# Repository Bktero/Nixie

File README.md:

# Nixie

Some circuit deal to deal with Nixie tubes.

## Power supply
The circuit was made to turn on ИН-14 (IH-14 with latin alphabet) tubes. The output voltage can be adjusted between 70 V and 240 V, making it suitable for other kinds of tubes.

You can find more information on this circuit on my blog (in French): https://gradot.wordpress.com/2015/03/10/alimentation-tubes-nixie/

## Time reference generator
The circuit generates a stable time reference. This is a square clock signal. Jumpers allow to select either 1 Hz, 2 Hz or 4 Hz as the output frequency.

You can find more information on this circuit on my blog (in French) : https://gradot.wordpress.com/2015/12/22/generer-un-signal-a-1-hz-avec-des-portes-logiques/

## Other circuits
Still work-in-progress attempts. Come back later :)

## License
_A copy of the license is available in this repository._

Copyright Pierre Gradot 2015-2016

This documentation describes Open Hardware and is licensed under the CERN OHL v. 1.2.

You may redistribute and modify this documentation under the terms of the CERN OHL v.1.2. (http://ohwr.org/cernohl).
This documentation is distributed WITHOUT ANY EXPRESS OR IMPLIED WARRANTY, INCLUDING OF MERCHANTABILITY, SATISFACTORY QUALITY AND FITNESS FOR APARTICULAR PURPOSE.

Please see the CERN OHL v.1.2 for applicable conditions.

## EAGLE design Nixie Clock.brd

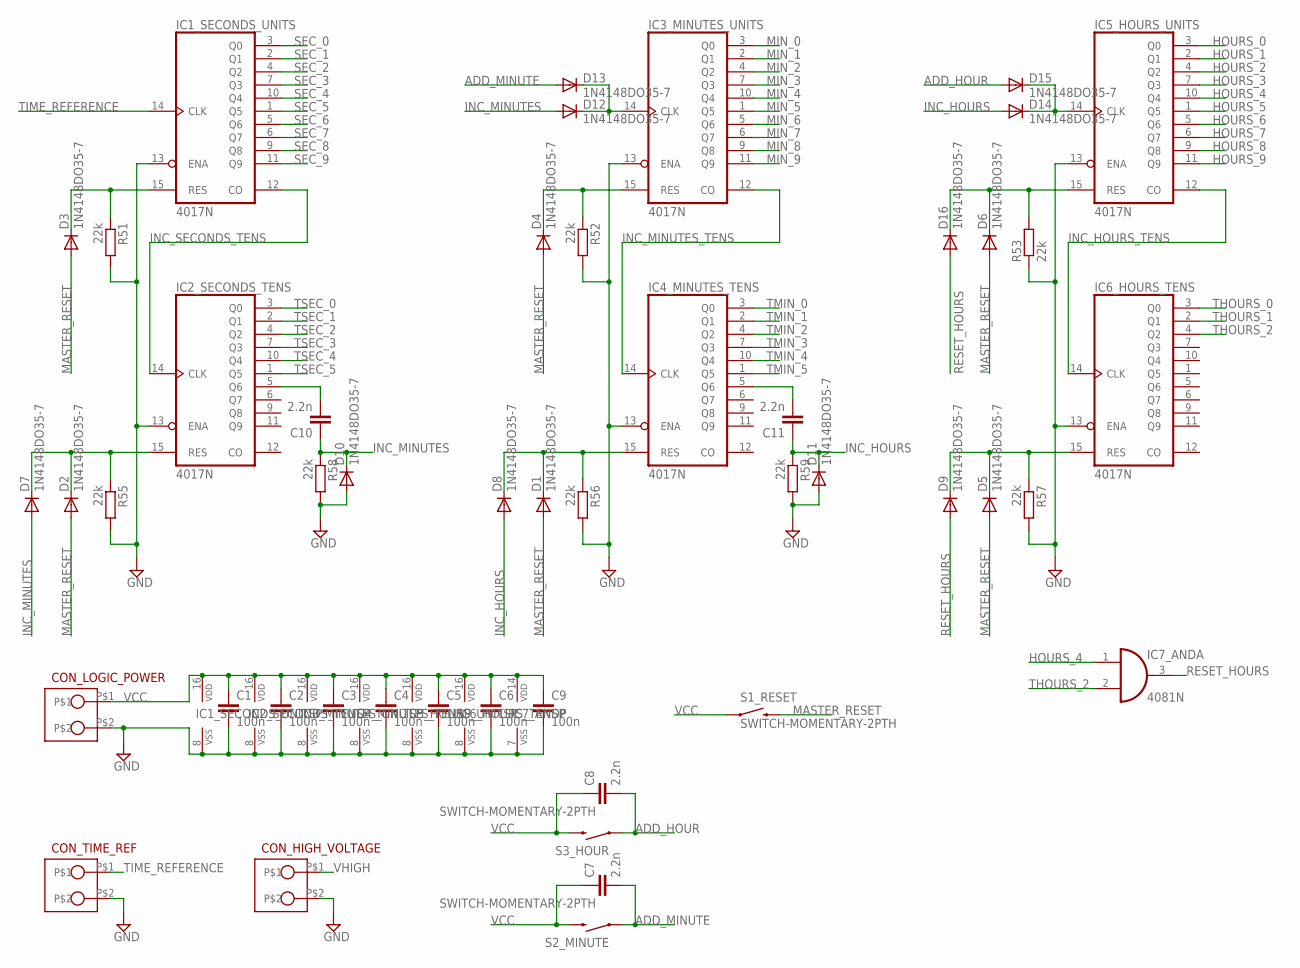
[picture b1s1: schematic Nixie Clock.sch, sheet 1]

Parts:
C1, C2, C3, C4, C5, C6, C9: 100n; C050-030X075
C7, C8, C10, C11: 2.2n; C050-030X075
CON_HIGH_VOLTAGE: CON_2_SIL; SIL_2_0.2INCH
CON_LOGIC_POWER: CON_2_SIL; SIL_2_0.2INCH
CON_TIME_REF: CON_2_SIL; SIL_2_0.2INCH
D1, D2, D3, D4, D5, D6, D7, D8, D9, D10, D11, D12, D13, D14, D15, D16: 1N4148DO35-7; DO35-7
IC1_SECONDS_UNITS, IC2_SECONDS_TENS, IC3_MINUTES_UNITS, IC4_MINUTES_TENS, IC5_HOURS_UNITS, IC6_HOURS_TENS: 4017N; DIL16
IC7_AND: 4081N; DIL14
R51, R52, R53, R55, R56, R57, R58, R59: 22k; 0207/10
S1_RESET, S2_MINUTE, S3_HOUR: SWITCH-MOMENTARY-2PTH; TACTILE-PTH

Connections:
ADD_HOUR: C8.2, D15.A, S3_HOUR.1
ADD_MINUTE: C7.2, D13.A, S2_MINUTE.1
GND: C1.2, C2.2, C3.2, C4.2, C5.2, C6.2, C9.2, CON_HIGH_VOLTAGE.P$2, CON_LOGIC_POWER.P$2, CON_TIME_REF.P$2, D10.A, D11.A, IC1_SECONDS_UNITS.8 (VSS), IC1_SECONDS_UNITS.13 (ENA), IC2_SECONDS_TENS.8 (VSS), IC2_SECONDS_TENS.13 (ENA), IC3_MINUTES_UNITS.8 (VSS), IC3_MINUTES_UNITS.13 (ENA), IC4_MINUTES_TENS.8 (VSS), IC4_MINUTES_TENS.13 (ENA), IC5_HOURS_UNITS.8 (VSS), IC5_HOURS_UNITS.13 (ENA), IC6_HOURS_TENS.8 (VSS), IC6_HOURS_TENS.13 (ENA), IC7_AND.7 (VSS), R51.2, R52.2, R53.1, R55.2, R56.2, R57.2, R58.2, R59.2; also elsewhere on the board
HOURS_0: IC5_HOURS_UNITS.3 (Q0); also elsewhere on the board
HOURS_1: IC5_HOURS_UNITS.2 (Q1); also elsewhere on the board
HOURS_2: IC5_HOURS_UNITS.4 (Q2); also elsewhere on the board
HOURS_3: IC5_HOURS_UNITS.7 (Q3); also elsewhere on the board
HOURS_4: IC5_HOURS_UNITS.10 (Q4), IC7_AND.1 (I0); also elsewhere on the board
HOURS_5: IC5_HOURS_UNITS.1 (Q5); also elsewhere on the board
HOURS_6: IC5_HOURS_UNITS.5 (Q6); also elsewhere on the board
HOURS_7: IC5_HOURS_UNITS.6 (Q7); also elsewhere on the board
HOURS_8: IC5_HOURS_UNITS.9 (Q8); also elsewhere on the board
HOURS_9: IC5_HOURS_UNITS.11 (Q9); also elsewhere on the board
INC_HOURS: C11.1, D8.A, D11.C, D14.A, R59.1
INC_HOURS_TENS: IC5_HOURS_UNITS.12 (CO), IC6_HOURS_TENS.14 (CLK)
INC_MINUTES: C10.1, D7.A, D10.C, D12.A, R58.1
INC_MINUTES_TENS: IC3_MINUTES_UNITS.12 (CO), IC4_MINUTES_TENS.14 (CLK)
INC_SECONDS_TENS: IC1_SECONDS_UNITS.12 (CO), IC2_SECONDS_TENS.14 (CLK)
MASTER_RESET: D1.A, D2.A, D3.A, D4.A, D5.A, D6.A, S1_RESET.3 (2)
MIN_0: IC3_MINUTES_UNITS.3 (Q0); also elsewhere on the board
MIN_1: IC3_MINUTES_UNITS.2 (Q1); also elsewhere on the board
MIN_2: IC3_MINUTES_UNITS.4 (Q2); also elsewhere on the board
MIN_3: IC3_MINUTES_UNITS.7 (Q3); also elsewhere on the board
MIN_4: IC3_MINUTES_UNITS.10 (Q4); also elsewhere on the board
MIN_5: IC3_MINUTES_UNITS.1 (Q5); also elsewhere on the board
MIN_6: IC3_MINUTES_UNITS.5 (Q6); also elsewhere on the board
MIN_7: IC3_MINUTES_UNITS.6 (Q7); also elsewhere on the board
MIN_8: IC3_MINUTES_UNITS.9 (Q8); also elsewhere on the board
MIN_9: IC3_MINUTES_UNITS.11 (Q9); also elsewhere on the board
unnamed: D2.C, D7.C, IC2_SECONDS_TENS.15 (RES), R55.1
unnamed: D3.C, IC1_SECONDS_UNITS.15 (RES), R51.1
unnamed: C10.2, IC2_SECONDS_TENS.5 (Q6)
unnamed: D1.C, D8.C, IC4_MINUTES_TENS.15 (RES), R56.1
unnamed: C11.2, IC4_MINUTES_TENS.5 (Q6)
unnamed: D4.C, IC3_MINUTES_UNITS.15 (RES), R52.1
unnamed: D12.C, D13.C, IC3_MINUTES_UNITS.14 (CLK)
unnamed: D5.C, D9.C, IC6_HOURS_TENS.15 (RES), R57.1
unnamed: D14.C, D15.C, IC5_HOURS_UNITS.14 (CLK)
unnamed: D6.C, D16.C, IC5_HOURS_UNITS.15 (RES), R53.2
RESET_HOURS: D9.A, D16.A, IC7_AND.3 (O)
SEC_0: IC1_SECONDS_UNITS.3 (Q0); also elsewhere on the board
SEC_1: IC1_SECONDS_UNITS.2 (Q1); also elsewhere on the board
SEC_2: IC1_SECONDS_UNITS.4 (Q2); also elsewhere on the board
SEC_3: IC1_SECONDS_UNITS.7 (Q3); also elsewhere on the board
SEC_4: IC1_SECONDS_UNITS.10 (Q4); also elsewhere on the board
SEC_5: IC1_SECONDS_UNITS.1 (Q5); also elsewhere on the board
SEC_6: IC1_SECONDS_UNITS.5 (Q6); also elsewhere on the board
SEC_7: IC1_SECONDS_UNITS.6 (Q7); also elsewhere on the board
SEC_8: IC1_SECONDS_UNITS.9 (Q8); also elsewhere on the board
SEC_9: IC1_SECONDS_UNITS.11 (Q9); also elsewhere on the board
THOURS_0: IC6_HOURS_TENS.3 (Q0); also elsewhere on the board
THOURS_1: IC6_HOURS_TENS.2 (Q1); also elsewhere on the board
THOURS_2: IC6_HOURS_TENS.4 (Q2), IC7_AND.2 (I1); also elsewhere on the board
TIME_REFERENCE: CON_TIME_REF.P$1, IC1_SECONDS_UNITS.14 (CLK)
TMIN_0: IC4_MINUTES_TENS.3 (Q0); also elsewhere on the board
TMIN_1: IC4_MINUTES_TENS.2 (Q1); also elsewhere on the board
TMIN_2: IC4_MINUTES_TENS.4 (Q2); also elsewhere on the board
TMIN_3: IC4_MINUTES_TENS.7 (Q3); also elsewhere on the board
TMIN_4: IC4_MINUTES_TENS.10 (Q4); also elsewhere on the board
TMIN_5: IC4_MINUTES_TENS.1 (Q5); also elsewhere on the board
TSEC_0: IC2_SECONDS_TENS.3 (Q0); also elsewhere on the board
TSEC_1: IC2_SECONDS_TENS.2 (Q1); also elsewhere on the board
TSEC_2: IC2_SECONDS_TENS.4 (Q2); also elsewhere on the board
TSEC_3: IC2_SECONDS_TENS.7 (Q3); also elsewhere on the board
TSEC_4: IC2_SECONDS_TENS.10 (Q4); also elsewhere on the board
TSEC_5: IC2_SECONDS_TENS.1 (Q5); also elsewhere on the board
VCC: C1.1, C2.1, C3.1, C4.1, C5.1, C6.1, C7.1, C8.1, C9.1, CON_LOGIC_POWER.P$1, IC1_SECONDS_UNITS.16 (VDD), IC2_SECONDS_TENS.16 (VDD), IC3_MINUTES_UNITS.16 (VDD), IC4_MINUTES_TENS.16 (VDD), IC5_HOURS_UNITS.16 (VDD), IC6_HOURS_TENS.16 (VDD), IC7_AND.14 (VDD), S1_RESET.1, S2_MINUTE.3 (2), S3_HOUR.3 (2)
VHIGH: CON_HIGH_VOLTAGE.P$1; also elsewhere on the board

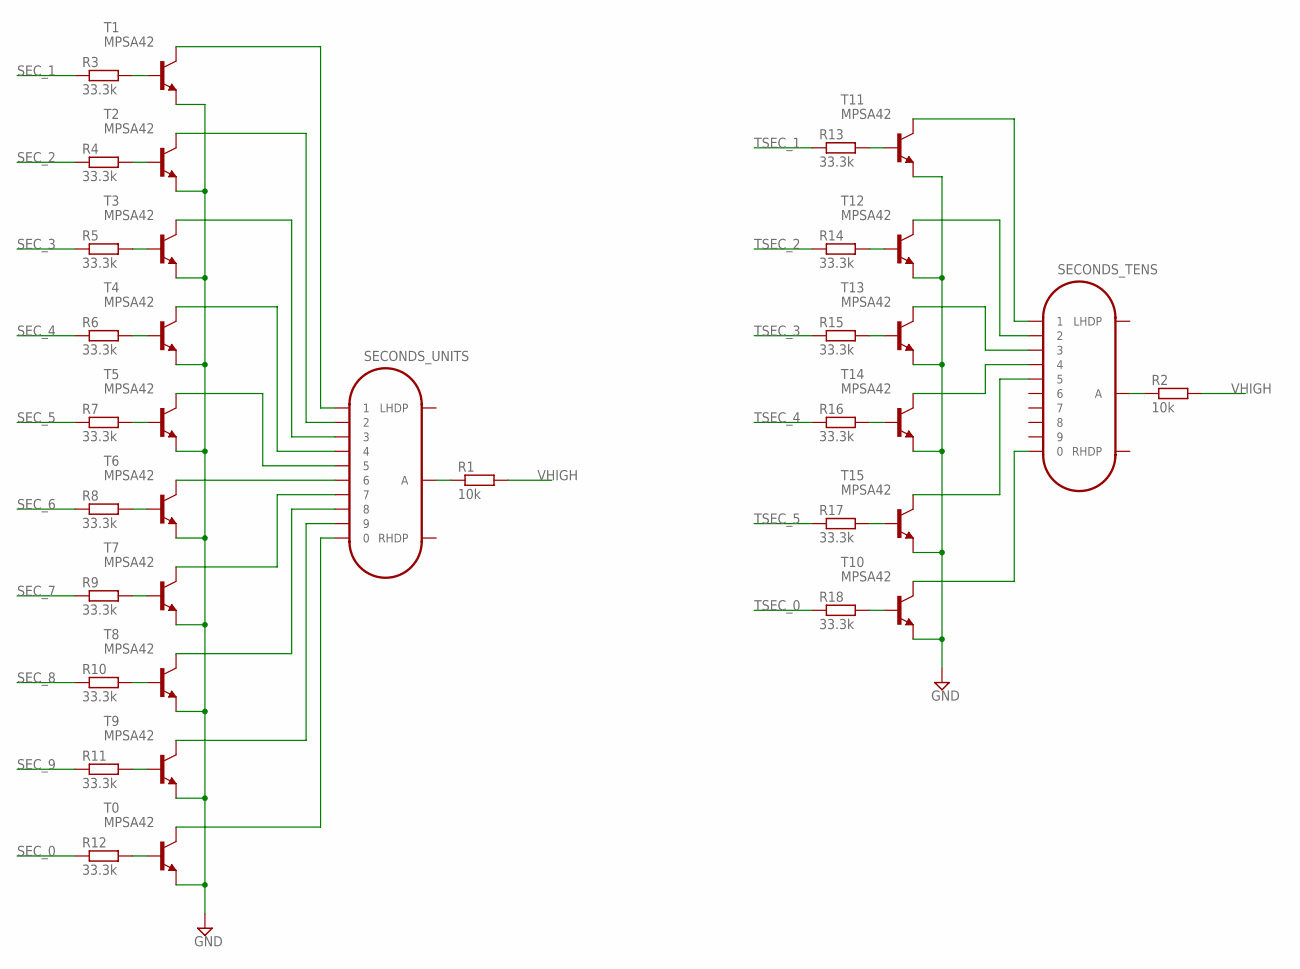
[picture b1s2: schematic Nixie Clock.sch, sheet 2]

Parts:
R1, R2: 10k; 0207/2V
R3, R4, R5, R6, R7, R8, R9, R10, R11, R12, R13, R14, R15, R16, R17, R18: 33.3k; 0207/10
SECONDS_TENS: IN-14BIG_PADS; IN-14-BIG-PADS
SECONDS_UNITS: IN-14BIG_PADS; IN-14-BIG-PADS
T0, T1, T2, T3, T4, T5, T6, T7, T8, T9, T10, T11, T12, T13, T14, T15: MPSA42; TO92

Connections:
GND: T0.1 (E), T1.1 (E), T2.1 (E), T3.1 (E), T4.1 (E), T5.1 (E), T6.1 (E), T7.1 (E), T8.1 (E), T9.1 (E), T10.1 (E), T11.1 (E), T12.1 (E), T13.1 (E), T14.1 (E), T15.1 (E); also elsewhere on the board
unnamed: R6.2, T4.2 (B)
unnamed: R7.2, T5.2 (B)
unnamed: R8.2, T6.2 (B)
unnamed: R9.2, T7.2 (B)
unnamed: R10.2, T8.2 (B)
unnamed: R11.2, T9.2 (B)
unnamed: R12.2, T0.2 (B)
unnamed: R1.1, SECONDS_UNITS.A
unnamed: R2.1, SECONDS_TENS.A
unnamed: R13.2, T11.2 (B)
unnamed: R14.2, T12.2 (B)
unnamed: R15.2, T13.2 (B)
unnamed: R16.2, T14.2 (B)
unnamed: R17.2, T15.2 (B)
unnamed: R18.2, T10.2 (B)
unnamed: R3.2, T1.2 (B)
unnamed: R4.2, T2.2 (B)
unnamed: R5.2, T3.2 (B)
unnamed: SECONDS_TENS.1, T11.3 (C)
unnamed: SECONDS_TENS.2, T12.3 (C)
unnamed: SECONDS_TENS.3, T13.3 (C)
unnamed: SECONDS_TENS.4, T14.3 (C)
unnamed: SECONDS_TENS.5, T15.3 (C)
unnamed: SECONDS_TENS.0, T10.3 (C)
unnamed: SECONDS_UNITS.1, T1.3 (C)
unnamed: SECONDS_UNITS.2, T2.3 (C)
unnamed: SECONDS_UNITS.3, T3.3 (C)
unnamed: SECONDS_UNITS.4, T4.3 (C)
unnamed: SECONDS_UNITS.5, T5.3 (C)
unnamed: SECONDS_UNITS.6, T6.3 (C)
unnamed: SECONDS_UNITS.0, T0.3 (C)
unnamed: SECONDS_UNITS.9, T9.3 (C)
unnamed: SECONDS_UNITS.8, T8.3 (C)
unnamed: SECONDS_UNITS.7, T7.3 (C)
SEC_0: R12.1; also elsewhere on the board
SEC_1: R3.1; also elsewhere on the board
SEC_2: R4.1; also elsewhere on the board
SEC_3: R5.1; also elsewhere on the board
SEC_4: R6.1; also elsewhere on the board
SEC_5: R7.1; also elsewhere on the board
SEC_6: R8.1; also elsewhere on the board
SEC_7: R9.1; also elsewhere on the board
SEC_8: R10.1; also elsewhere on the board
SEC_9: R11.1; also elsewhere on the board
TSEC_0: R18.1; also elsewhere on the board
TSEC_1: R13.1; also elsewhere on the board
TSEC_2: R14.1; also elsewhere on the board
TSEC_3: R15.1; also elsewhere on the board
TSEC_4: R16.1; also elsewhere on the board
TSEC_5: R17.1; also elsewhere on the board
VHIGH: R1.2, R2.2; also elsewhere on the board

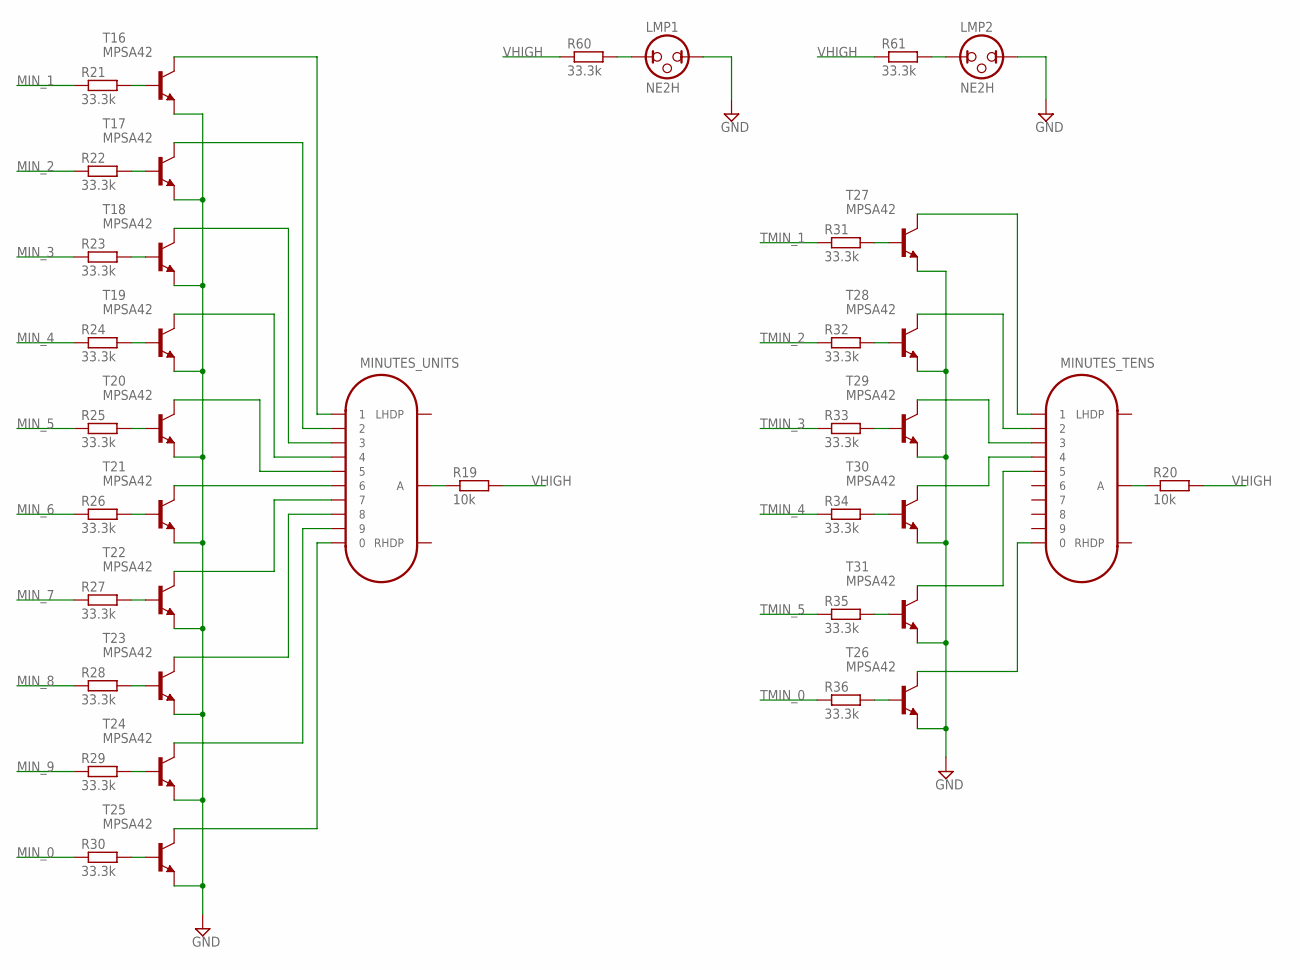
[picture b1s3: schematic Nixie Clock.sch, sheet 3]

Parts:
LMP1, LMP2: NE2H; NEON_LAMP_0.1_INCH
MINUTES_TENS: IN-14BIG_PADS; IN-14-BIG-PADS
MINUTES_UNITS: IN-14BIG_PADS; IN-14-BIG-PADS
R19, R20: 10k; 0207/2V
R21, R22, R23, R24, R25, R26, R27, R28, R29, R30, R31, R32, R33, R34, R35, R36: 33.3k; 0207/10
R60, R61: 33.3k; 0207/2V
T16, T17, T18, T19, T20, T21, T22, T23, T24, T25, T26, T27, T28, T29, T30, T31: MPSA42; TO92

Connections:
GND: LMP1.P$2 (2), LMP2.P$2 (2), T16.1 (E), T17.1 (E), T18.1 (E), T19.1 (E), T20.1 (E), T21.1 (E), T22.1 (E), T23.1 (E), T24.1 (E), T25.1 (E), T26.1 (E), T27.1 (E), T28.1 (E), T29.1 (E), T30.1 (E), T31.1 (E); also elsewhere on the board
MIN_0: R30.1; also elsewhere on the board
MIN_1: R21.1; also elsewhere on the board
MIN_2: R22.1; also elsewhere on the board
MIN_3: R23.1; also elsewhere on the board
MIN_4: R24.1; also elsewhere on the board
MIN_5: R25.1; also elsewhere on the board
MIN_6: R26.1; also elsewhere on the board
MIN_7: R27.1; also elsewhere on the board
MIN_8: R28.1; also elsewhere on the board
MIN_9: R29.1; also elsewhere on the board
unnamed: R24.2, T19.2 (B)
unnamed: R25.2, T20.2 (B)
unnamed: R26.2, T21.2 (B)
unnamed: R27.2, T22.2 (B)
unnamed: R28.2, T23.2 (B)
unnamed: R29.2, T24.2 (B)
unnamed: R30.2, T25.2 (B)
unnamed: MINUTES_UNITS.A, R19.1
unnamed: MINUTES_TENS.A, R20.1
unnamed: R31.2, T27.2 (B)
unnamed: R32.2, T28.2 (B)
unnamed: R33.2, T29.2 (B)
unnamed: R34.2, T30.2 (B)
unnamed: R35.2, T31.2 (B)
unnamed: R36.2, T26.2 (B)
unnamed: R21.2, T16.2 (B)
unnamed: R22.2, T17.2 (B)
unnamed: R23.2, T18.2 (B)
unnamed: MINUTES_TENS.1, T27.3 (C)
unnamed: MINUTES_TENS.2, T28.3 (C)
unnamed: MINUTES_TENS.3, T29.3 (C)
unnamed: MINUTES_TENS.4, T30.3 (C)
unnamed: MINUTES_TENS.5, T31.3 (C)
unnamed: MINUTES_TENS.0, T26.3 (C)
unnamed: MINUTES_UNITS.1, T16.3 (C)
unnamed: MINUTES_UNITS.2, T17.3 (C)
unnamed: MINUTES_UNITS.3, T18.3 (C)
unnamed: MINUTES_UNITS.4, T19.3 (C)
unnamed: MINUTES_UNITS.5, T20.3 (C)
unnamed: MINUTES_UNITS.6, T21.3 (C)
unnamed: MINUTES_UNITS.0, T25.3 (C)
unnamed: MINUTES_UNITS.9, T24.3 (C)
unnamed: MINUTES_UNITS.8, T23.3 (C)
unnamed: MINUTES_UNITS.7, T22.3 (C)
unnamed: LMP2.P$1 (1), R61.2
unnamed: LMP1.P$1 (1), R60.2
TMIN_0: R36.1; also elsewhere on the board
TMIN_1: R31.1; also elsewhere on the board
TMIN_2: R32.1; also elsewhere on the board
TMIN_3: R33.1; also elsewhere on the board
TMIN_4: R34.1; also elsewhere on the board
TMIN_5: R35.1; also elsewhere on the board
VHIGH: R19.2, R20.2, R60.1, R61.1; also elsewhere on the board

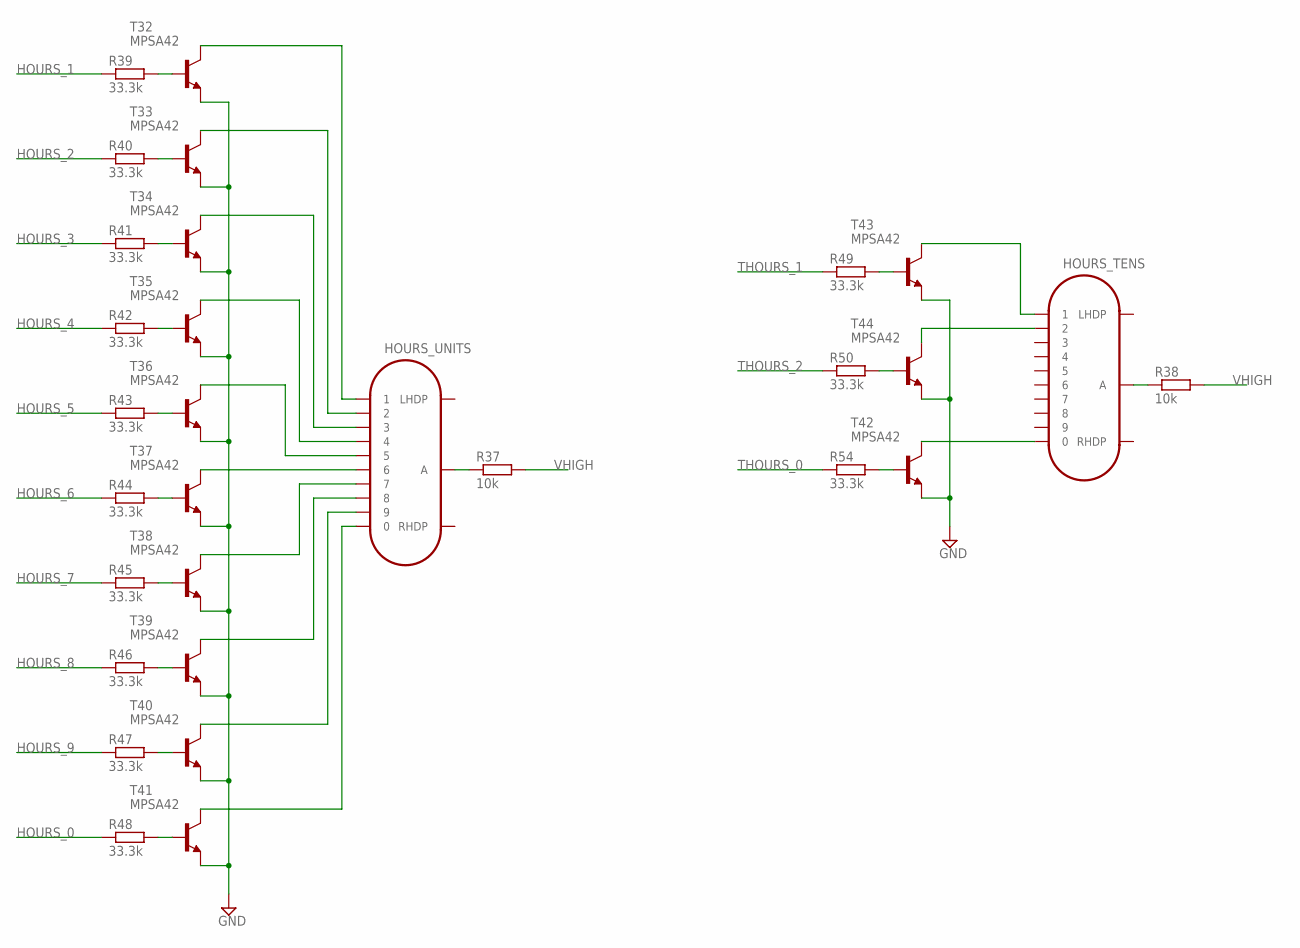
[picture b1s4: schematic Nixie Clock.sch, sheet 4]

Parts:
HOURS_TENS: IN-14BIG_PADS; IN-14-BIG-PADS
HOURS_UNITS: IN-14BIG_PADS; IN-14-BIG-PADS
R37, R38: 10k; 0207/2V
R39, R40, R41, R42, R43, R44, R45, R46, R47, R48, R49, R50, R54: 33.3k; 0207/10
T32, T33, T34, T35, T36, T37, T38, T39, T40, T41, T42, T43, T44: MPSA42; TO92

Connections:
GND: T32.1 (E), T33.1 (E), T34.1 (E), T35.1 (E), T36.1 (E), T37.1 (E), T38.1 (E), T39.1 (E), T40.1 (E), T41.1 (E), T42.1 (E), T43.1 (E), T44.1 (E); also elsewhere on the board
HOURS_0: R48.1; also elsewhere on the board
HOURS_1: R39.1; also elsewhere on the board
HOURS_2: R40.1; also elsewhere on the board
HOURS_3: R41.1; also elsewhere on the board
HOURS_4: R42.1; also elsewhere on the board
HOURS_5: R43.1; also elsewhere on the board
HOURS_6: R44.1; also elsewhere on the board
HOURS_7: R45.1; also elsewhere on the board
HOURS_8: R46.1; also elsewhere on the board
HOURS_9: R47.1; also elsewhere on the board
unnamed: R42.2, T35.2 (B)
unnamed: R43.2, T36.2 (B)
unnamed: R44.2, T37.2 (B)
unnamed: R45.2, T38.2 (B)
unnamed: R46.2, T39.2 (B)
unnamed: R47.2, T40.2 (B)
unnamed: R48.2, T41.2 (B)
unnamed: HOURS_UNITS.A, R37.1
unnamed: HOURS_TENS.A, R38.1
unnamed: R49.2, T43.2 (B)
unnamed: R50.2, T44.2 (B)
unnamed: HOURS_TENS.0, T42.3 (C)
unnamed: R54.2, T42.2 (B)
unnamed: R39.2, T32.2 (B)
unnamed: R40.2, T33.2 (B)
unnamed: R41.2, T34.2 (B)
unnamed: HOURS_TENS.1, T43.3 (C)
unnamed: HOURS_TENS.2, T44.3 (C)
unnamed: HOURS_UNITS.7, T38.3 (C)
unnamed: HOURS_UNITS.1, T32.3 (C)
unnamed: HOURS_UNITS.2, T33.3 (C)
unnamed: HOURS_UNITS.3, T34.3 (C)
unnamed: HOURS_UNITS.4, T35.3 (C)
unnamed: HOURS_UNITS.5, T36.3 (C)
unnamed: HOURS_UNITS.6, T37.3 (C)
unnamed: HOURS_UNITS.0, T41.3 (C)
unnamed: HOURS_UNITS.9, T40.3 (C)
unnamed: HOURS_UNITS.8, T39.3 (C)
THOURS_0: R54.1; also elsewhere on the board
THOURS_1: R49.1; also elsewhere on the board
THOURS_2: R50.1; also elsewhere on the board
VHIGH: R37.2, R38.2; also elsewhere on the board

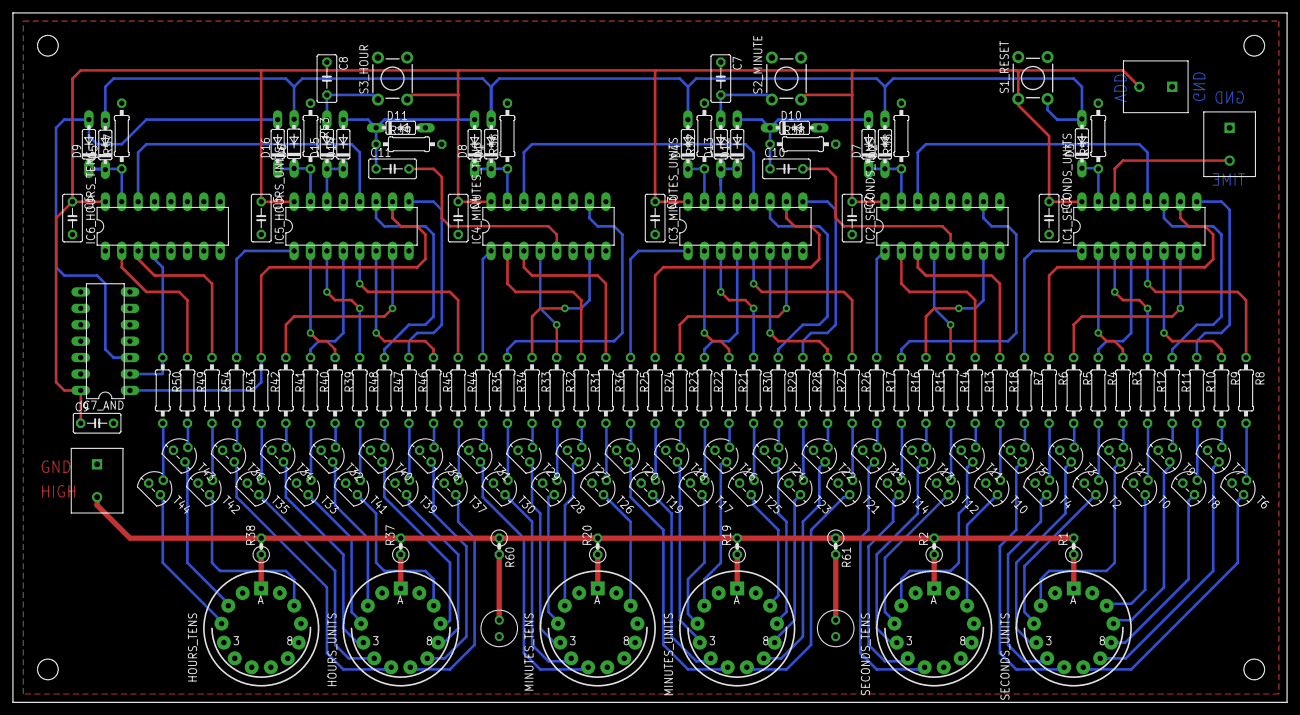
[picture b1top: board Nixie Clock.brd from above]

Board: 2 copper layers, 197.2 x 106.7 mm, 154 parts (0 on the bottom side), 166 nets.

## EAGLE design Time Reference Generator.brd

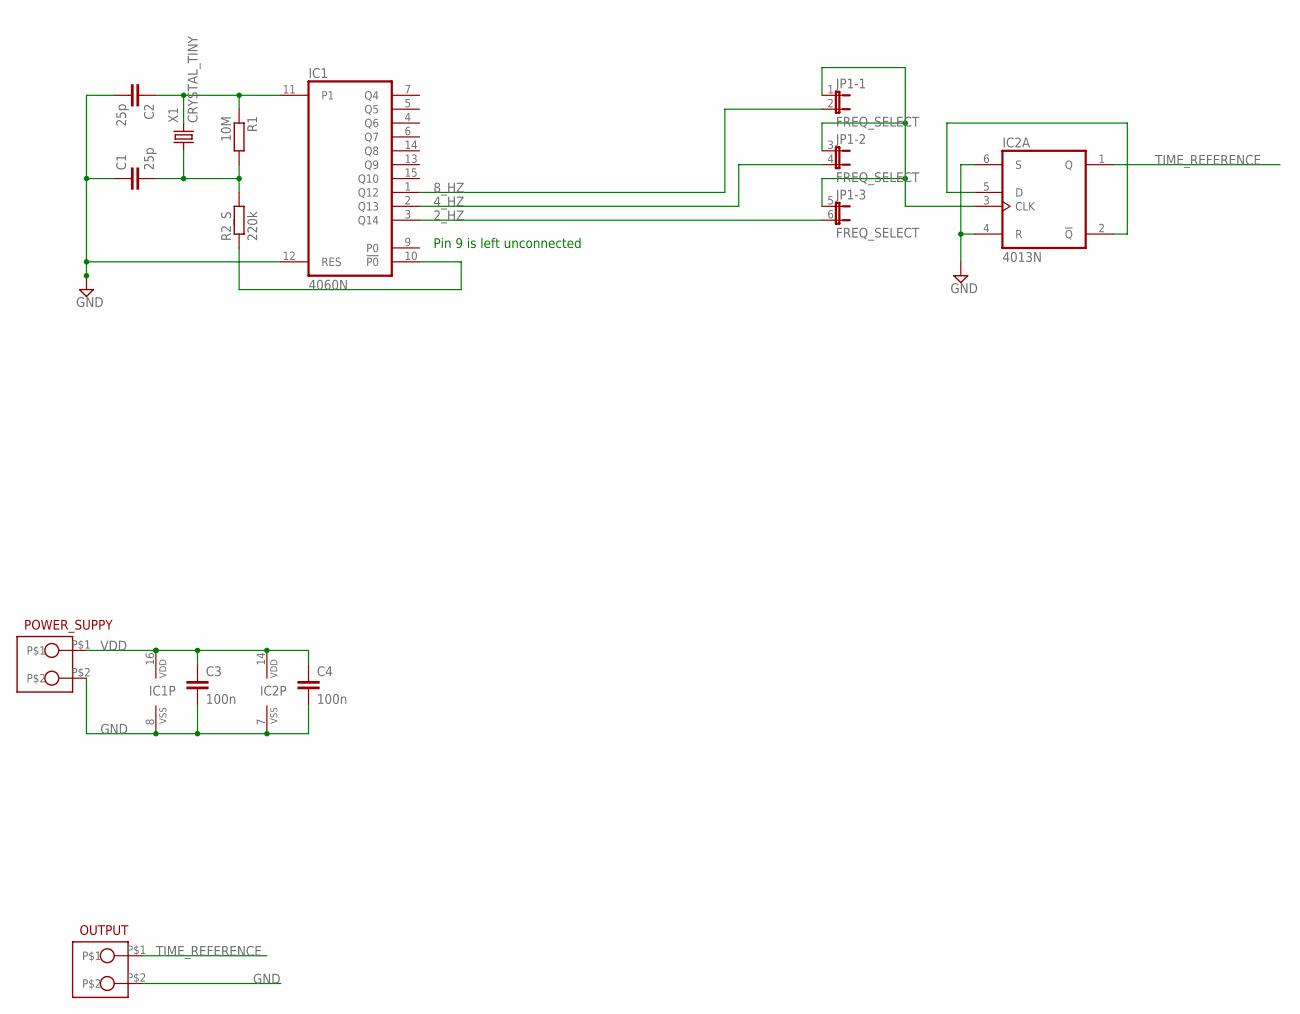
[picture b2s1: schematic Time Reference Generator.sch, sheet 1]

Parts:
C1, C2: 25p; C050-025X075
C3, C4: 100n; C050-030X075
IC1: 4060N; DIL16
IC2: 4013N; DIL14
JP1: FREQ_SELECT; JP3Q
OUTPUT: CON_2_SIL; SIL_2_0.2INCH
POWER_SUPPY: CON_2_SIL; SIL_2_0.2INCH
R1: 10M; 0207/10
R2_S: 220k; 0207/10
X1: CRYSTAL_TINY; WATCH-3X8-SPACED

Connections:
2_HZ: IC1.3 (Q14), JP1.6 (2)
4_HZ: IC1.2 (Q13), JP1.4 (2)
8_HZ: IC1.1 (Q12), JP1.2
GND: C1.1, C2.2, C3.2, C4.2, IC1.8 (VSS), IC1.12 (RES), IC2.4 (R), IC2.6 (S), IC2.7 (VSS), OUTPUT.P$2, POWER_SUPPY.P$2
unnamed: C2.1, IC1.11 (P1), R1.1, X1.2
unnamed: C1.2, R1.2, R2_S.2, X1.1
unnamed: IC1.10 (!P0), R2_S.1
unnamed: IC2.2 (!Q), IC2.5 (D)
unnamed: IC2.3 (CLK), JP1.1, JP1.3 (1), JP1.5 (1)
TIME_REFERENCE: IC2.1 (Q), OUTPUT.P$1
VDD: C3.1, C4.1, IC1.16 (VDD), IC2.14 (VDD), POWER_SUPPY.P$1

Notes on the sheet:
Pin 9 is left unconnected

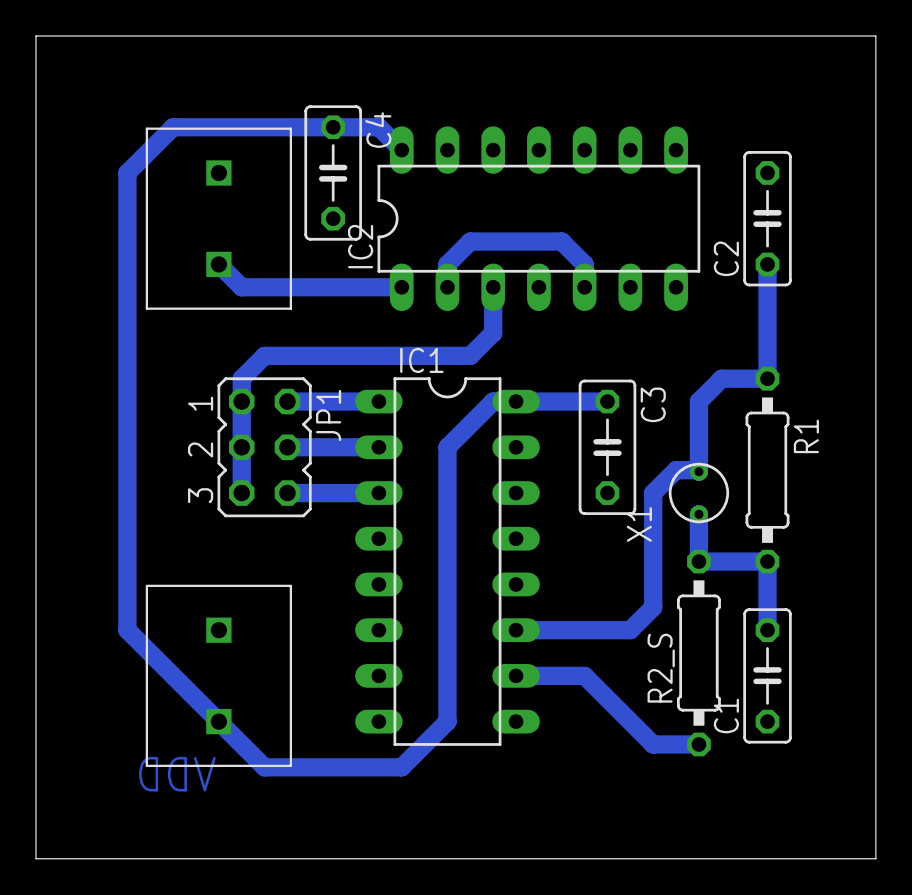
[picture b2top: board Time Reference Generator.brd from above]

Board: 2 copper layers, 46.7 x 45.7 mm, 12 parts (0 on the bottom side), 11 nets.

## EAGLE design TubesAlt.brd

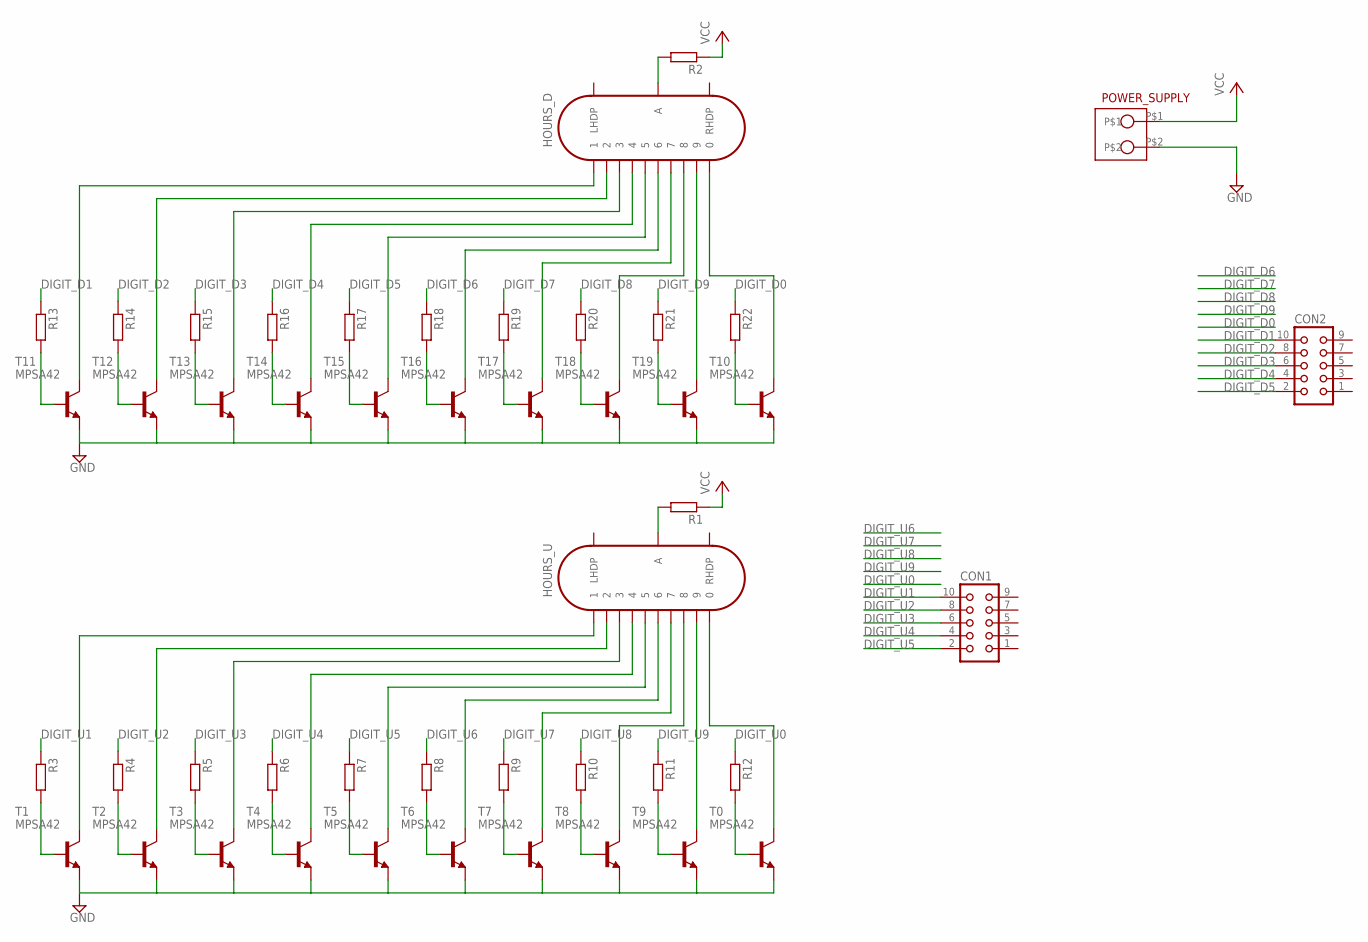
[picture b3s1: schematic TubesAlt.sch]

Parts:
CON1, CON2: CON10
HOURS_D: IN-14
HOURS_U: IN-14
POWER_SUPPLY: CON_2_SIL; SIL_2_0.2INCH
R1, R2, R3, R4, R5, R6, R7, R8, R9, R10, R11, R12, R13, R14, R15, R16, R17, R18, R19, R20, R21, R22: R-EU_0207/10; 0207/10
T0, T1, T2, T3, T4, T5, T6, T7, T8, T9, T10, T11, T12, T13, T14, T15, T16, T17, T18, T19: MPSA42; TO92

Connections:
DIGIT_D0: R22.1
DIGIT_D1: CON2.10, R13.1
DIGIT_D2: CON2.8, R14.1
DIGIT_D3: CON2.6, R15.1
DIGIT_D4: CON2.4, R16.1
DIGIT_D5: CON2.2, R17.1
DIGIT_D6: R18.1
DIGIT_D7: R19.1
DIGIT_D8: R20.1
DIGIT_D9: R21.1
DIGIT_U0: R12.1
DIGIT_U1: CON1.10, R3.1
DIGIT_U2: CON1.8, R4.1
DIGIT_U3: CON1.6, R5.1
DIGIT_U4: CON1.4, R6.1
DIGIT_U5: CON1.2, R7.1
DIGIT_U6: R8.1
DIGIT_U7: R9.1
DIGIT_U8: R10.1
DIGIT_U9: R11.1
GND: POWER_SUPPLY.P$2, T0.1 (E), T1.1 (E), T2.1 (E), T3.1 (E), T4.1 (E), T5.1 (E), T6.1 (E), T7.1 (E), T8.1 (E), T9.1 (E), T10.1 (E), T11.1 (E), T12.1 (E), T13.1 (E), T14.1 (E), T15.1 (E), T16.1 (E), T17.1 (E), T18.1 (E), T19.1 (E)
unnamed: HOURS_U.0, T0.3 (C)
unnamed: HOURS_U.9, T9.3 (C)
unnamed: R7.2, T5.2 (B)
unnamed: R8.2, T6.2 (B)
unnamed: R9.2, T7.2 (B)
unnamed: R12.2, T0.2 (B)
unnamed: R3.2, T1.2 (B)
unnamed: R5.2, T3.2 (B)
unnamed: R4.2, T2.2 (B)
unnamed: R6.2, T4.2 (B)
unnamed: R10.2, T8.2 (B)
unnamed: R11.2, T9.2 (B)
unnamed: HOURS_U.8, T8.3 (C)
unnamed: HOURS_U.7, T7.3 (C)
unnamed: HOURS_U.6, T6.3 (C)
unnamed: HOURS_U.5, T5.3 (C)
unnamed: HOURS_U.1, T1.3 (C)
unnamed: HOURS_U.4, T4.3 (C)
unnamed: HOURS_U.2, T2.3 (C)
unnamed: HOURS_D.0, T10.3 (C)
unnamed: HOURS_U.3, T3.3 (C)
unnamed: HOURS_D.9, T19.3 (C)
unnamed: HOURS_U.A, R1.2
unnamed: HOURS_D.8, T18.3 (C)
unnamed: HOURS_D.7, T17.3 (C)
unnamed: HOURS_D.6, T16.3 (C)
unnamed: HOURS_D.5, T15.3 (C)
unnamed: HOURS_D.2, T12.3 (C)
unnamed: HOURS_D.A, R2.2
unnamed: HOURS_D.3, T13.3 (C)
unnamed: HOURS_D.4, T14.3 (C)
unnamed: HOURS_D.1, T11.3 (C)
unnamed: R17.2, T15.2 (B)
unnamed: R18.2, T16.2 (B)
unnamed: R19.2, T17.2 (B)
unnamed: R22.2, T10.2 (B)
unnamed: R13.2, T11.2 (B)
unnamed: R15.2, T13.2 (B)
unnamed: R14.2, T12.2 (B)
unnamed: R16.2, T14.2 (B)
unnamed: R20.2, T18.2 (B)
unnamed: R21.2, T19.2 (B)
VCC: POWER_SUPPLY.P$1, R1.1, R2.1

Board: 2 copper layers, 47 parts (0 on the bottom side), 54 nets, no tracks yet.

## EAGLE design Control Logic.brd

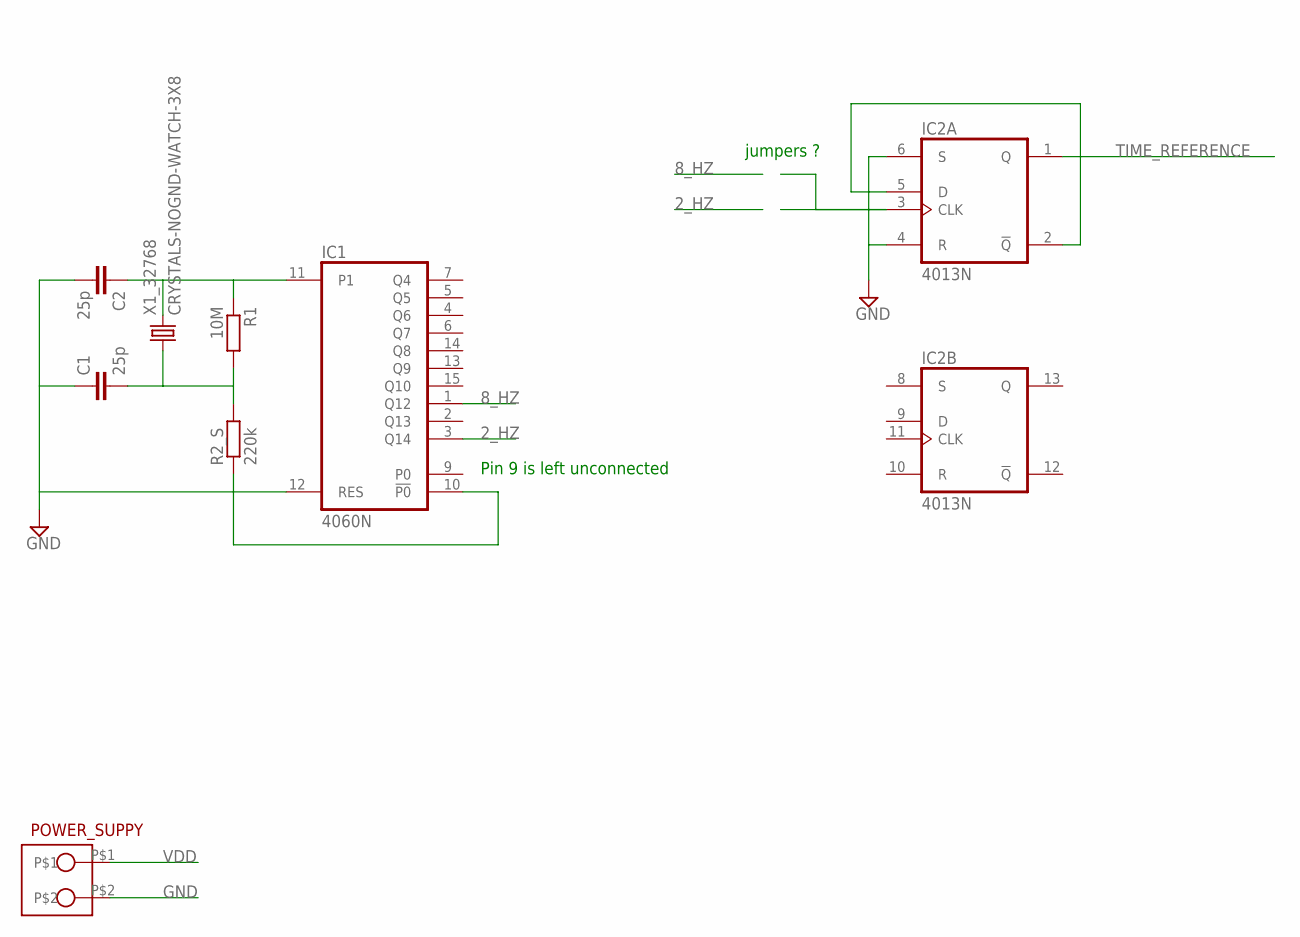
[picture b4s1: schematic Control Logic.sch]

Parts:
C1, C2: 25p; C050-025X075
IC1: 4060N; DIL16
IC2: 4013N; DIL14
POWER_SUPPY: CON_2_SIL; SIL_2_0.2INCH
R1: 10M; 0207/10
R2_S: 220k; 0207/10
X1_32768: CRYSTALS-NOGND-WATCH-3X8; WATCH-3X8

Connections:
2_HZ: IC1.3 (Q14)
8_HZ: IC1.1 (Q12)
GND: C1.1, C2.2, IC1.12 (RES), IC2.4 (R), IC2.6 (S), POWER_SUPPY.P$2
unnamed: C2.1, IC1.11 (P1), R1.1, X1_32768.2
unnamed: C1.2, R1.2, R2_S.2, X1_32768.1
unnamed: IC1.10 (!P0), R2_S.1
unnamed: IC2.2 (!Q), IC2.5 (D)
TIME_REFERENCE: IC2.1 (Q)
VDD: IC1.16 (VDD), IC2.14 (VDD), POWER_SUPPY.P$1
VSS: IC1.8 (VSS), IC2.7 (VSS)

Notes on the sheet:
Pin 9 is left unconnected
jumpers ?

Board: 2 copper layers, 8 parts (0 on the bottom side), 7 nets, no tracks yet.

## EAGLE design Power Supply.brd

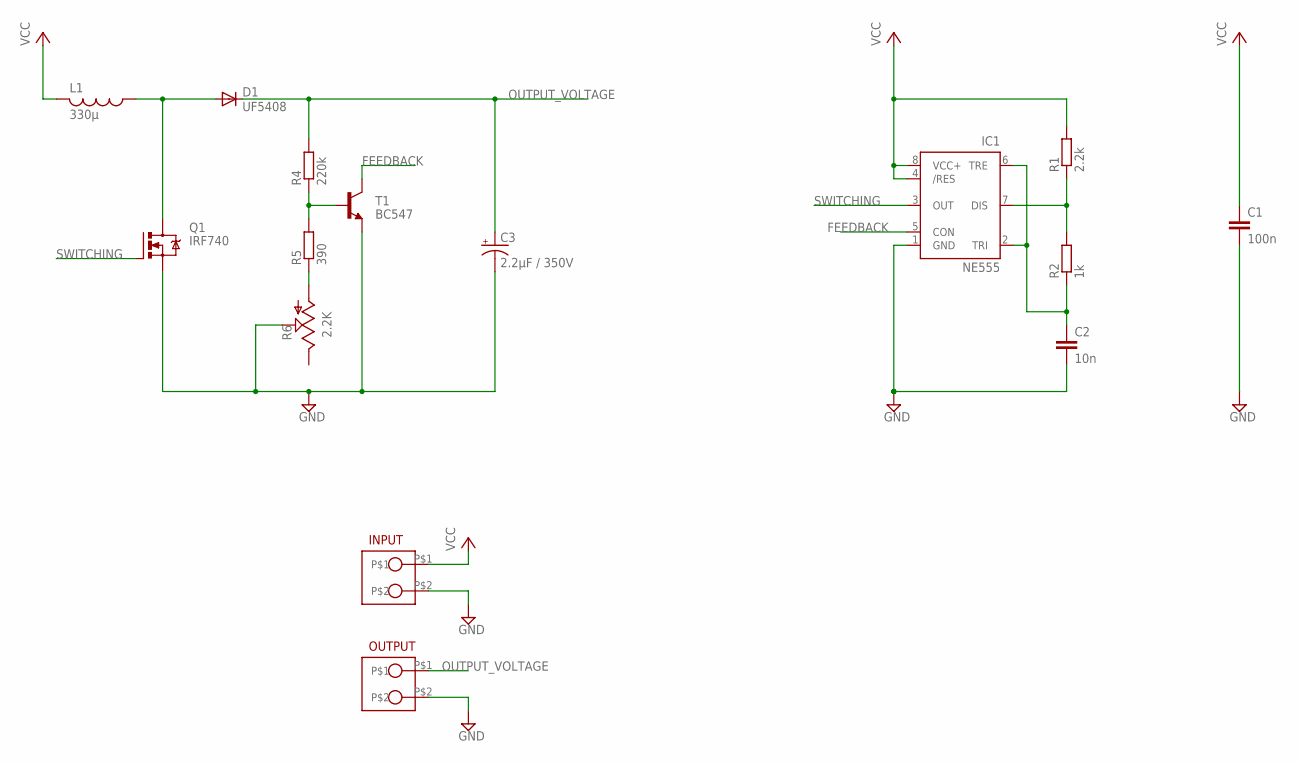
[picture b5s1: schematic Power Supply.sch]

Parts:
C1: 100n; C050-030X075
C2: 10n; C050-030X075
C3: 2.2µF / 350V; TAP5-80
D1: UF5408; DO201-15
IC1: NE555; DIL-08
INPUT: CON_2_SIL; SIL_2_0.2INCH
L1: 330µ; 6000-XXXX-RC
OUTPUT: CON_2_SIL; SIL_2_0.2INCH
Q1: IRF740; TO220BV
R1: 2.2k; 0207/10
R2: 1k; 0207/10
R4: 220k; 0207/10
R5: 390; 0207/10
R6: 2.2K; CA9V
T1: BC547; TO92

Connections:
FEEDBACK: IC1.5 (CON), T1.3 (C)
GND: C1.2, C2.2, C3.-, IC1.1 (GND), INPUT.P$2, OUTPUT.P$2, Q1.S, R6.S, T1.1 (E)
unnamed: D1.A, L1.1, Q1.D
unnamed: IC1.7 (DIS), R1.1, R2.2
unnamed: R5.1, R6.A
unnamed: R4.1, R5.2, T1.2 (B)
unnamed: C2.1, IC1.2 (TRI), IC1.6 (TRE), R2.1
OUTPUT_VOLTAGE: C3.+, D1.C, OUTPUT.P$1, R4.2
SWITCHING: IC1.3 (OUT), Q1.G
VCC: C1.1, IC1.4 (/RES), IC1.8 (VCC+), INPUT.P$1, L1.2, R1.2

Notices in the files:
parts and their libraries:
SparkFun-Electromechanical: Licensing: Creative Commons ShareAlike 4.0 International - https://creativecommons.org/licenses/by-sa/4.0
